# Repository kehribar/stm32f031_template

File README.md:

## STM32F031 Template

Ongoing process for creating a easy to use, open development environment for STM32F031 chips.

### Notes
* Uses internal 8Mhz RC oscillator to generate 48Mhz system clock using PLL
* Programming and debugging requires OpenOCD installed on the system.
* "STM32F4 Discovery" board is used as a "ST-LINK/V2" JTAG adapter.

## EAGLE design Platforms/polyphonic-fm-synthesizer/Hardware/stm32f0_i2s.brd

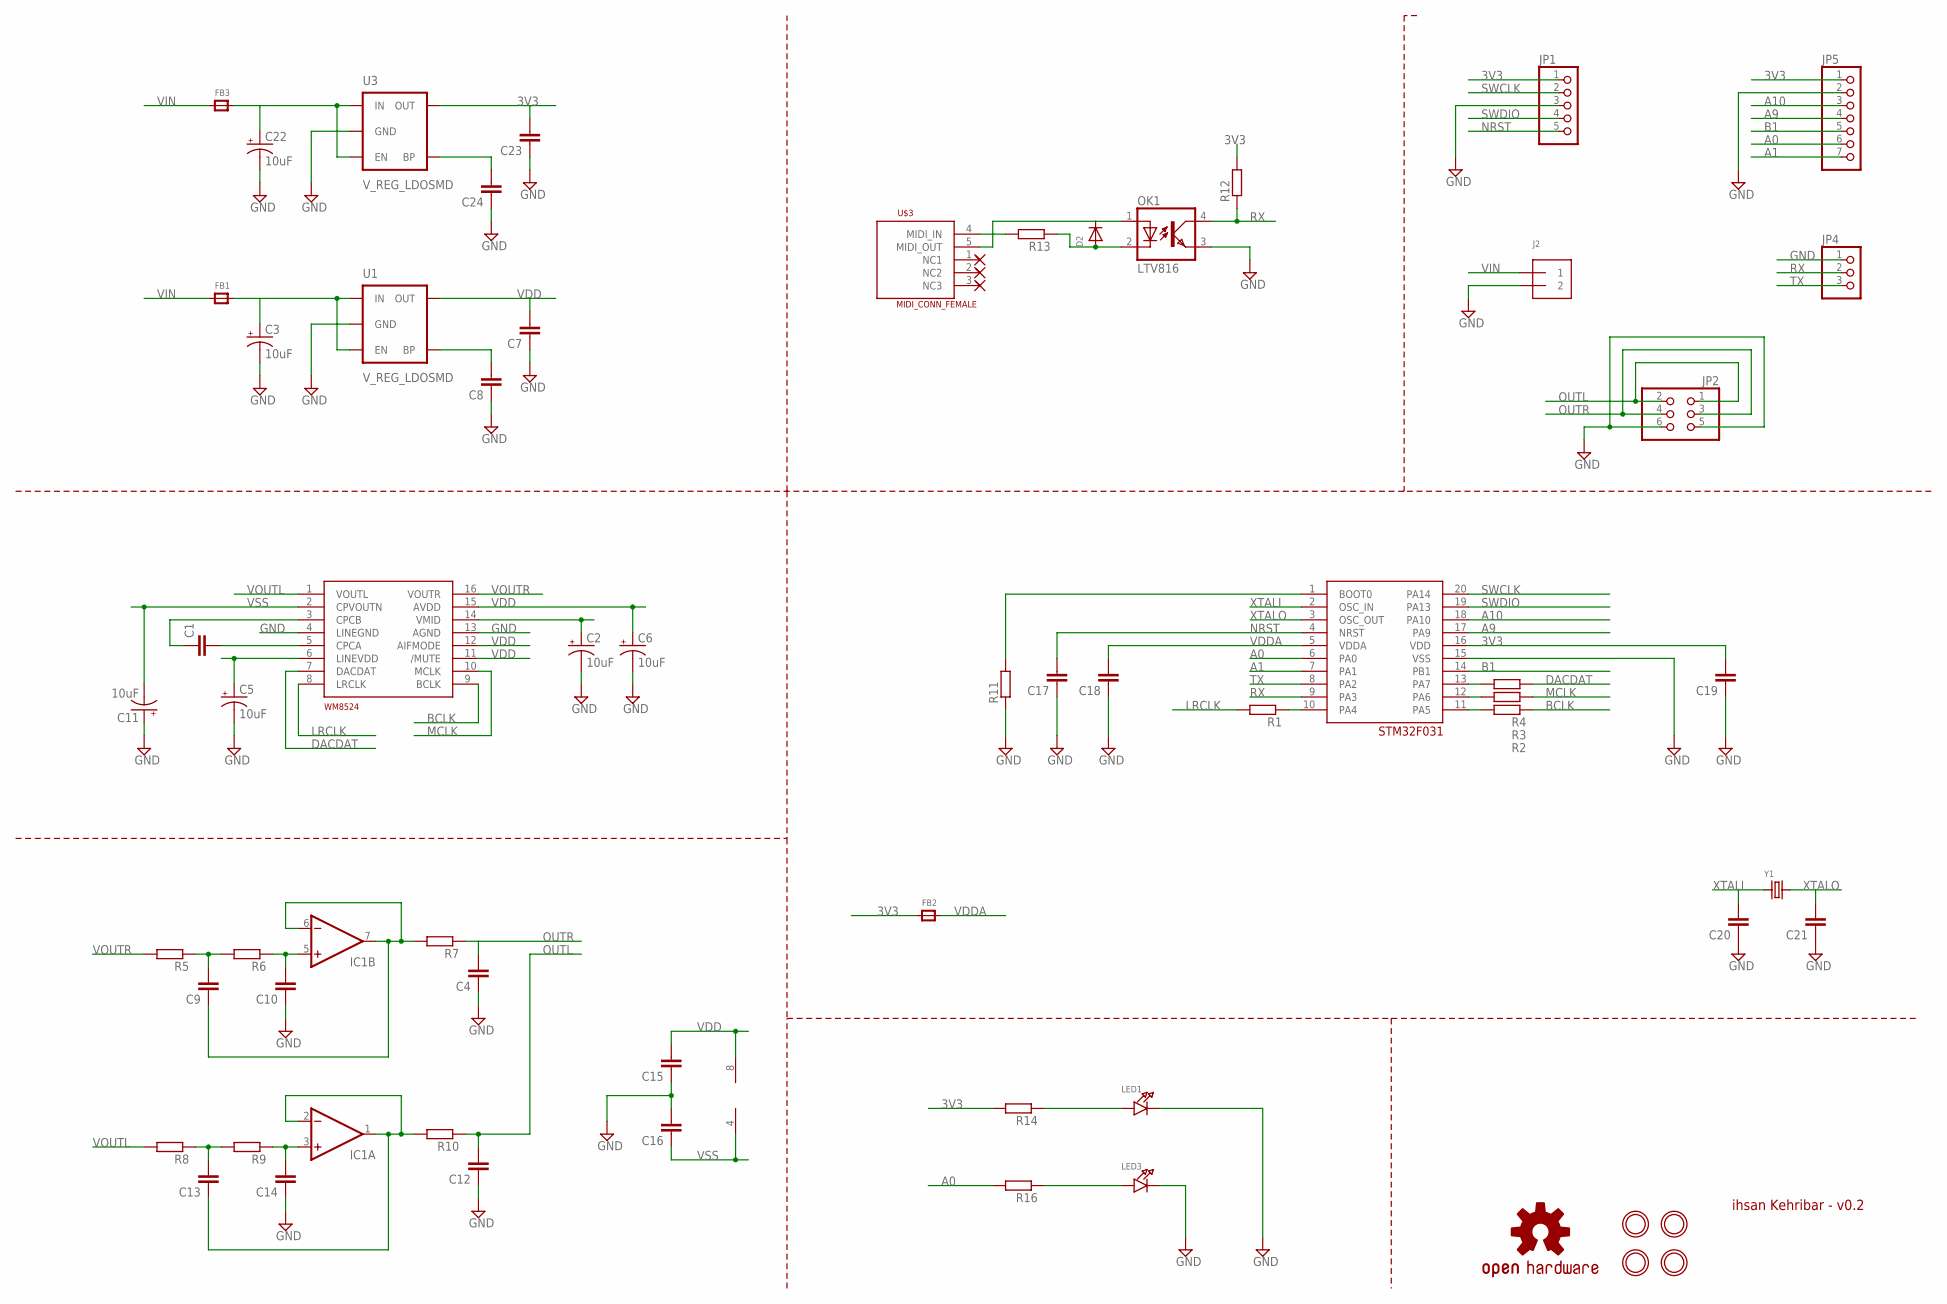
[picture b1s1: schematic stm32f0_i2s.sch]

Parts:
C1, C4, C7, C8, C9, C10, C12, C13, C14, C15, C16, C17, C18, C19, C20, C21, C23, C24: C-EUC0805; C0805
C2, C3, C5, C6, C11, C22: 10uF; EIA3216
D2: DIODEDO-1N4148; DO-1N4148
FB1, FB2, FB3: FERRITE0805; 0805
IC1: TL082D; SO08
J2: TERMBLOCK_1X2; TERMBLOCK_1X2-3.5MM
JP1: HEADER-1X5ROUND; 1X05_ROUND
JP2: PINHD-2X3; 2X03
JP4: HEADER-1X3ROUND; 1X03_ROUND
JP5: HEADER-1X7ROUND; 1X07_ROUND
LED1, LED3: LED1206; CHIPLED_1206
LOGO1: OSHW-LOGOM; OSHW-LOGO-M
OK1: LTV816; DIL04
R1, R2, R3, R4, R5, R6, R7, R8, R9, R10, R11, R12, R13, R14, R16: R-EU_R0805; R0805
U1, U3: V_REG_LDOSMD; SOT23-5
U$1: IHSAN_WM8524; TSSOP16
U$2: IHSAN_STM32F031; TSSOP20
U$3: MIDI_CONN_FEMALE; DIN_5_FEMALE
U$4, U$5, U$6, U$7: MOUNTINGHOLE3.0THIN; MOUNTINGHOLE_3.0_PLATEDTHIN
Y1: CRYSTALTHIN32K; CRYSTAL_4.9X1.8

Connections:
3V3: C19.2, C23.2, FB2.1, JP1.1, JP5.1, R12.2, R14.2, U3.5 (OUT), U$2.16 (VDD)
A0: JP5.6, R16.2, U$2.6 (PA0)
A1: JP5.7, U$2.7 (PA1)
A9: JP5.4, U$2.17 (PA9)
A10: JP5.3, U$2.18 (PA10)
B1: JP5.5, U$2.14 (PB1)
BCLK: R2.1, U$1.9 (BCLK)
DACDAT: R4.1, U$1.7 (DACDAT)
GND: C2.C (-), C3.C (-), C4.1, C5.C (-), C6.C (-), C7.1, C8.1, C10.1, C11.A (+), C12.1, C14.1, C15.1, C16.2, C17.1, C18.1, C19.1, C20.1, C21.1, C22.C (-), C23.1, C24.1, J2.2, JP1.3, JP2.5, JP2.6, JP4.1, JP5.2, LED1.C, LED3.C, OK1.3 (EMIT), R11.1, U1.2 (GND), U3.2 (GND), U$1.4 (LINEGND), U$1.13 (AGND), U$2.15 (VSS)
LRCLK: R1.2, U$1.8 (LRCLK)
MCLK: R3.1, U$1.10 (MCLK)
unnamed: C1.1, U$1.3 (CPCB)
unnamed: C1.2, U$1.5 (CPCA)
unnamed: C2.A (+), U$1.14 (VMID)
unnamed: C5.A (+), U$1.6 (LINEVDD)
unnamed: C22.A (+), FB3.2, U3.1 (IN), U3.3 (EN)
unnamed: R1.1, U$2.10 (PA4)
unnamed: R2.2, U$2.11 (PA5)
unnamed: R3.2, U$2.12 (PA6)
unnamed: R4.2, U$2.13 (PA7)
unnamed: C9.2, R5.1, R6.2
unnamed: C10.2, IC1.5 (+IN), R6.1
unnamed: C3.A (+), FB1.2, U1.1 (IN), U1.3 (EN)
unnamed: C8.2, U1.4 (BP)
unnamed: C9.1, IC1.6 (-IN), IC1.7 (OUT), R7.2
unnamed: D2.C, OK1.1 (A), U$3.5 (MIDI_OUT)
unnamed: C13.2, R8.1, R9.2
unnamed: C14.2, IC1.3 (+IN), R9.1
unnamed: C13.1, IC1.1 (OUT), IC1.2 (-IN), R10.2
unnamed: D2.A, OK1.2 (C), R13.1
unnamed: R11.2, U$2.1 (BOOT0)
unnamed: C24.2, U3.4 (BP)
unnamed: R13.2, U$3.4 (MIDI_IN)
unnamed: LED3.A, R16.1
unnamed: LED1.A, R14.1
NRST: C17.2, JP1.5, U$2.4 (NRST)
OUTL: C12.2, JP2.1, JP2.2, R10.1
OUTR: C4.2, JP2.3, JP2.4, R7.1
RX: JP4.2, OK1.4 (COL), R12.1, U$2.9 (PA3)
SWCLK: JP1.2, U$2.20 (PA14)
SWDIO: JP1.4, U$2.19 (PA13)
TX: JP4.3, U$2.8 (PA2)
VDD: C6.A (+), C7.2, C15.2, IC1.8 (V+), U1.5 (OUT), U$1.11 (/MUTE), U$1.12 (AIFMODE), U$1.15 (AVDD)
VDDA: C18.2, FB2.2, U$2.5 (VDDA)
VIN: FB1.1, FB3.1, J2.1
VOUTL: R8.2, U$1.1 (VOUTL)
VOUTR: R5.2, U$1.16 (VOUTR)
VSS: C11.C (-), C16.1, IC1.4 (V-), U$1.2 (CPVOUTN)
XTALI: C20.2, U$2.2 (OSC_IN), Y1.1
XTALO: C21.2, U$2.3 (OSC_OUT), Y1.2

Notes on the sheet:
ihsan Kehribar - v0.2

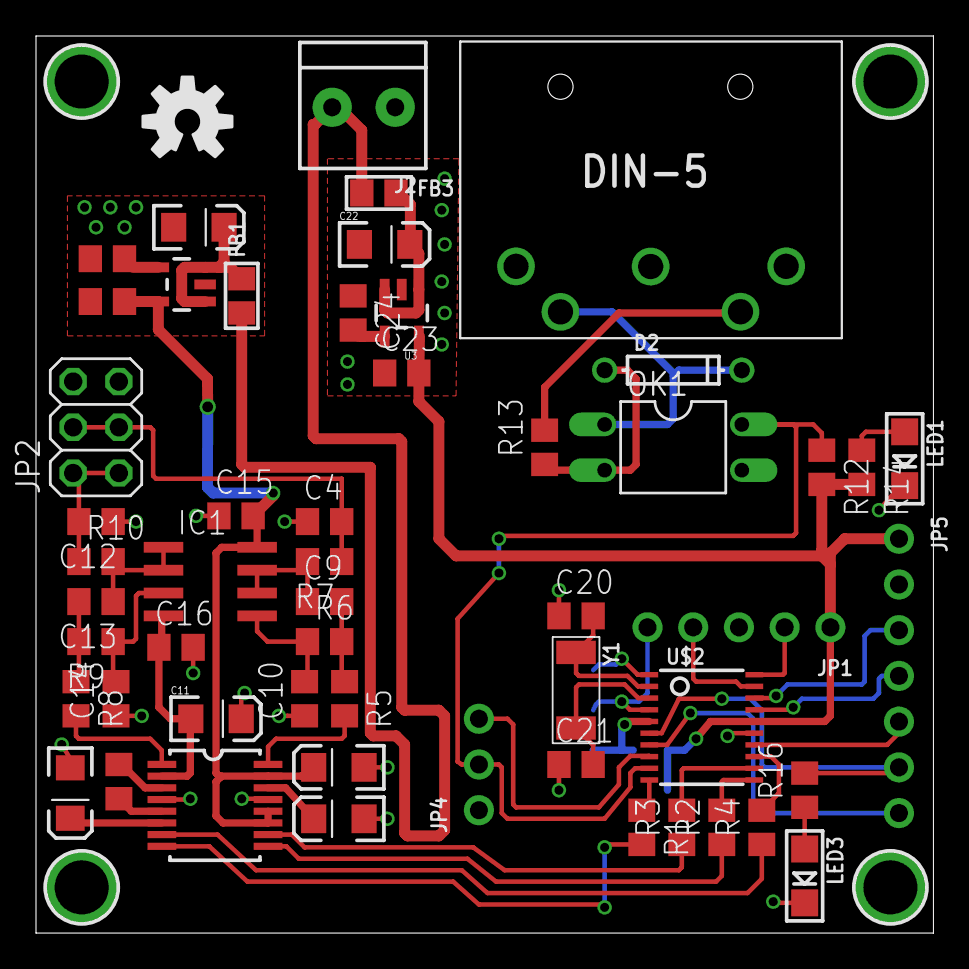
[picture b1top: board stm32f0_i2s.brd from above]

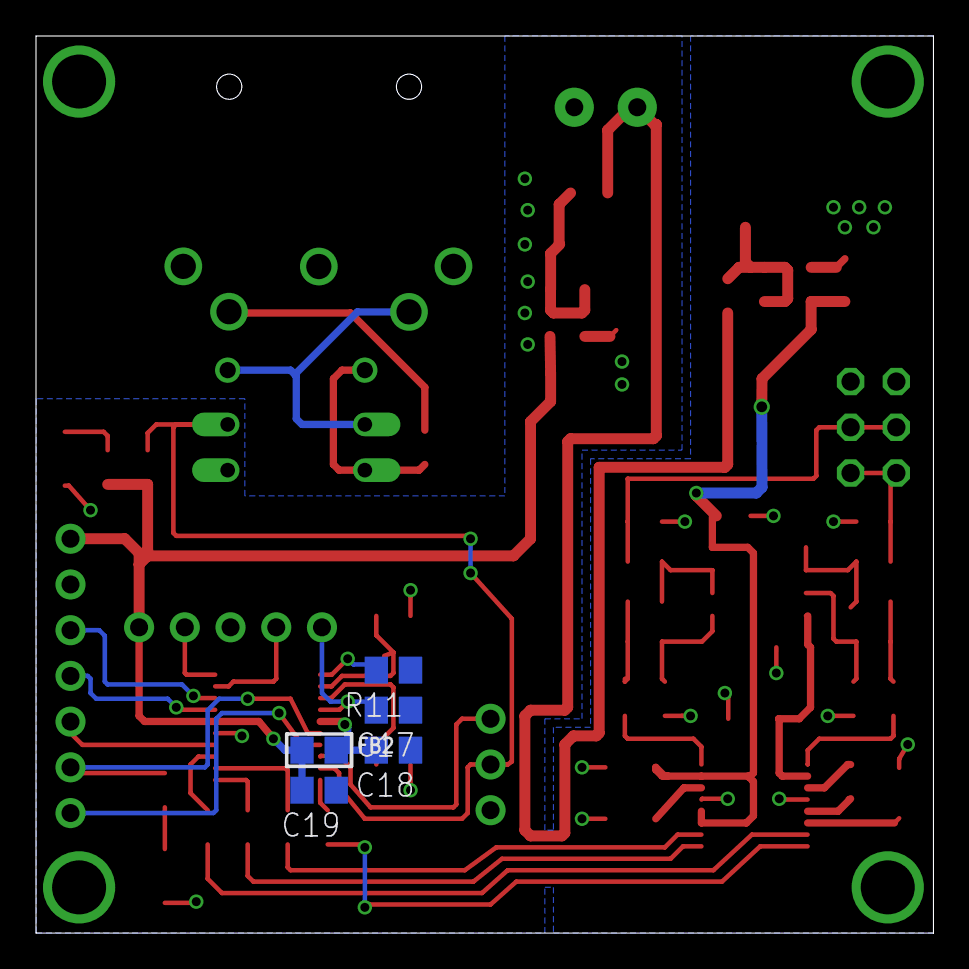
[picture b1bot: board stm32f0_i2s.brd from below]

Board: 2 copper layers, 49.9 x 49.8 mm, 63 parts (5 on the bottom side), 50 nets.

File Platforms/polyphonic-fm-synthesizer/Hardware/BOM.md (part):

Please feel free to open Pull Requests with other distributors for parts. 

| Part | Value              | Package         | Description                                      | Bürklin   | Mouser               | Comments                                                       |
|------|--------------------|-----------------|--------------------------------------------------|-----------|----------------------|----------------------------------------------------------------|
| C1   | 1uF               | 0805            | Ceramic Capacitor                                | 53 D 2422 |                      |                                                                |
| C7   | 1uF                | 0805            | Ceramic Capacitor                                | 53 D 2422 |                      |                                                                |
| C8   | 1uF                | 0805            | Ceramic Capacitor                                | 53 D 2422 |                      |                                                                |
| C23  | 1uF                | 0805            | Ceramic Capacitor                                | 53 D 2422 |                      |                                                                |
| C24  | 1uF                | 0805            | Ceramic Capacitor                                | 53 D 2422 |                      |                                                                |
| C2   | 10µF               | EIA3216         | Tantalum Capacitor                               | 25 D 3338 |                      |                                                                |
| C3   | 10µF               | EIA3216         | Tantalum Capacitor                               | 25 D 3338 |                      |                                                                |
| C5   | 10µF               | EIA3216         | Tantalum Capacitor                               | 25 D 3338 |                      |                                                                |
| C6   | 10µF               | EIA3216         | Tantalum Capacitor                               | 25 D 3338 |                      |                                                                |
| C11  | 10µF               | EIA3216         | Tantalum Capacitor                               | 25 D 3338 |                      |                                                                |
| C22  | 10µF               | EIA3216         | Tantalum Capacitor                               | 25 D 3338 |                      |                                                                |
| C4   | 4.7nF              | 0805            | Ceramic Capacitor                                | 46 D 6316 |                      |                                                                |
| C9   | 4.7nF              | 0805            | Ceramic Capacitor                                | 46 D 6316 |                      |                                                                |
| C10  | 4.7nF              | 0805            | Ceramic Capacitor                                | 46 D 6316 |                      |                                                                |
| C12  | 4.7nF              | 0805            | Ceramic Capacitor                                | 46 D 6316 |                      |                                                                |
| C13  | 4.7nF              | 0805            | Ceramic Capacitor                                | 46 D 6316 |                      |                                                                |
| C14  | 4.7nF              | 0805            | Ceramic Capacitor                                | 46 D 6316 |                      |                                                                |
| C15  | 4.7nF              | 0805            | Ceramic Capacitor                                | 46 D 6316 |                      |                                                                |
| C16  | 4.7nF              | 0805            | Ceramic Capacitor                                | 46 D 6316 |                      |                                                                |
| C17  | 100nF              | 0805            | Ceramic Capacitor                                | 56 D 288  |                      |                                                                |
| C18  | 100nF              | 0805            | Ceramic Capacitor                                | 56 D 288  |                      |                                                                |
| C19  | 100nF              | 0805            | CAPACITOR, European symbol                       | 56 D 288  |                      |                                                                |
| D2   | 1N4148             | DO              | Diode                                            | 26 S 8140 |                      |                                                                |
| FB1  | 10 µH              | 0805            | Ferrite Bead                                     | 74 D 3034 |                      |                                                                |
| FB2  | 10 µH              | 0805            | Ferrite Bead                                     | 74 D 3034 |                      |                                                                |
| FB3  | 10 µH              | 0805            | Ferrite Bead                                     | 74 D 3034 |                      |                                                                |
| IC1  | MCP 6002-I/SN      | SO08            | OP AMP                                           | 49 S 5790 | 579-MCP6002-I/SN     |                                                                |
| LED1 | RED LED            | 1206            | LED                                              | 66 S 9134 |                      |                                                                |
| LED3 | GREEN LED          | 1206            | LED                                              | 66 S 9138 |                      |                                                                |
| OK1  | LTV-816            | DIL04           | Opto Coupler                                     |           | 859-LTV-816          |                                                                |
| R1   | 100                | 0805            | Resistor                                         | 11 E 148  |                      |                                                                |
| R2   | 100                | 0805            | Resistor                                         | 11 E 148  |                      |                                                                |
| R3   | 100                | 0805            | Resistor                                         | 11 E 148  |                      |                                                                |
| R4   | 100                | 0805            | Resistor                                         | 11 E 148  |                      |                                                                |
| R14  | 100                | 0805            | Resistor                                         | 11 E 148  |                      |                                                                |
| R16  | 100                | 0805            | Resistor                                         | 11 E 148  |                      |                                                                |
| R12  | 100                | 0805            | Resistor                                         | 11 E 148  |                      |                                                                |
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
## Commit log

2015-07-28 Style fix.
2015-08-01 Datasheets added.
2015-08-01 Digital IO macro created
2015-08-02 Use internal clock source for PLL
2015-08-02 Openocd based flash method and GDB debug method added.
2015-08-02 Cleaner main example.
2015-08-02 New hardware layer functions added.
2015-08-02 modified: README.md
2015-08-02 Folder based structure for seperate projects
2015-08-03 USART example added.
2015-08-03 Modifications ...
2015-09-06 Double buffered DMA based I2S transmission example using 16bits data width.
2015-09-06 Pin names in comments. DMA priority change
2015-09-09 Add DDD based debug session command. Increased buffer size for DMA.
2015-10-11 24bit I2S DMA example added.
2015-10-21 Synth example initial commit.
2015-10-21 Revert back the change.
2015-10-21 Synth example
2015-10-21 Remove misleading comment
2015-10-27 Stereo panning and lfo added. Also, sustain part is added to the envelopes
2015-11-01 Running status support for the MIDI. Low frequency modulation of frequency modulation support is added.
2015-12-06 small changes.
2016-04-30 added 3d printed case, and imported board + schematic for fm synth
2016-05-06 added BOM, tweaked mounting holes
2016-05-07 fixed typos, improved layout
2016-05-07 fixed ascii layout

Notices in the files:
parts and their libraries:
SparkFun-DigitalIC_ihsan: Licensing: CC v3.0 Share-Alike You are welcome to use this library for commercial purposes.
microbuilder: This work is placed in the public domain, and may be freely used for commercial and non-commercial work with the following conditions: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
